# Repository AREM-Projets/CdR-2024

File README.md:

# CdR-2024
Repo contenant l'ensemble des documents liés à la Coupe de France de Robotique (ou CdR pour Coupe de Robotique) 2024.

## Organisation du repo

Le dossier [Generalites](./Generalites) contient l'analyse du règlement ainsi que des ressources diverses. 

Le code, les PCBs et les modélisations 3D sont dans les dossiers PAMIs et Robot, selon leur utilisation.

La documentation associée à chaque partie du projet doit se trouver dans le README du dossier associé.

## Ajout de contenu

N'hésitez pas à ajouter vos tests divers sur ce repo.

Si vous pensez avoir cassé quelque chose, contactez le respo informatique.

## Dates de la CDR : 7 au 11 mai 2024

Merci à tous !!!

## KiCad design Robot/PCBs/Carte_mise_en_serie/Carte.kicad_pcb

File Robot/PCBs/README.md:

# PCBs - Robot principal

Chaque PCB doit être dans un dossier séparé. Il doit être présent à la fois sous la forme d'un schéma modifiable et au formt `.pdf` pour facilité de lecture.

Dans ce README, une description rapide (1-2 lignes) de son utilité doit être présente, ainsi que le nom des personnes qui l'ont designé.

# Liste des PCBs

### PCB n°1: ALIM 5V

Le PCB prend en entrée une tension 24V DC et la convertie en une tension 5V DC. On a 3A par buck et 4 ports de sortie JST-XH, soit 6A max au total pour 8 ports de sortie. La tension de sortie des bucks est réglable grâce au potentiomètre. Ce PCB peut donc être utilisé pour d'autres tension d'entrées et de sorties. De même, on peut récupérer directement le 24V pour les moteurs grâce à un port XT-60.  

Desiger : Cyril, Eliott

### PCB n°2: carte de mise en série

Permet de mettre en série deux batteries 12V.

Designer : Eliott

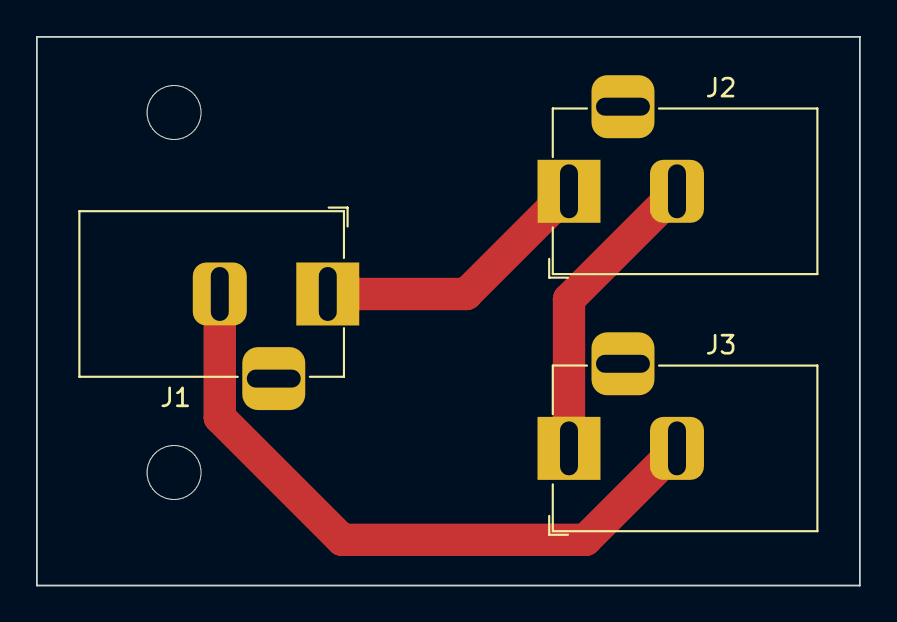
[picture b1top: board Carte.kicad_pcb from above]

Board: 2 copper layers, 45.7 x 30.5 mm, 5 parts (0 on the bottom side), 2 nets.

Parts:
H1, H2: MountingHole; MountingHole_3mm
J1, J2, J3: Conn_01x02_Pin; BarrelJack_Horizontal

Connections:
unnamed: J1.1, J2.1
unnamed: J1.2, J1.3, J2.2, J3.1, J3.2, J3.3

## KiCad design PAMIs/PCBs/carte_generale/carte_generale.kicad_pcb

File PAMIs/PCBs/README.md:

# PCBs - PAMIs

Chaque PCB doit être dans un dossier séparé. Il doit être présent à la fois sous la forme d'un schéma modifiable et au formt `.pdf` pour facilité de lecture.

Dans ce README, une description rapide (1-2 lignes) de son utilité doit être présente, ainsi que le nom des personnes qui l'ont designé.

# Liste des PCBs

### Nom du PCB

Ca sert à quoi ???

Desiger : Quelqu'un, quelqu'un d'autre...

### Nom du PCB n°2

Et lui il sert à quoi ???

Designer : Lui

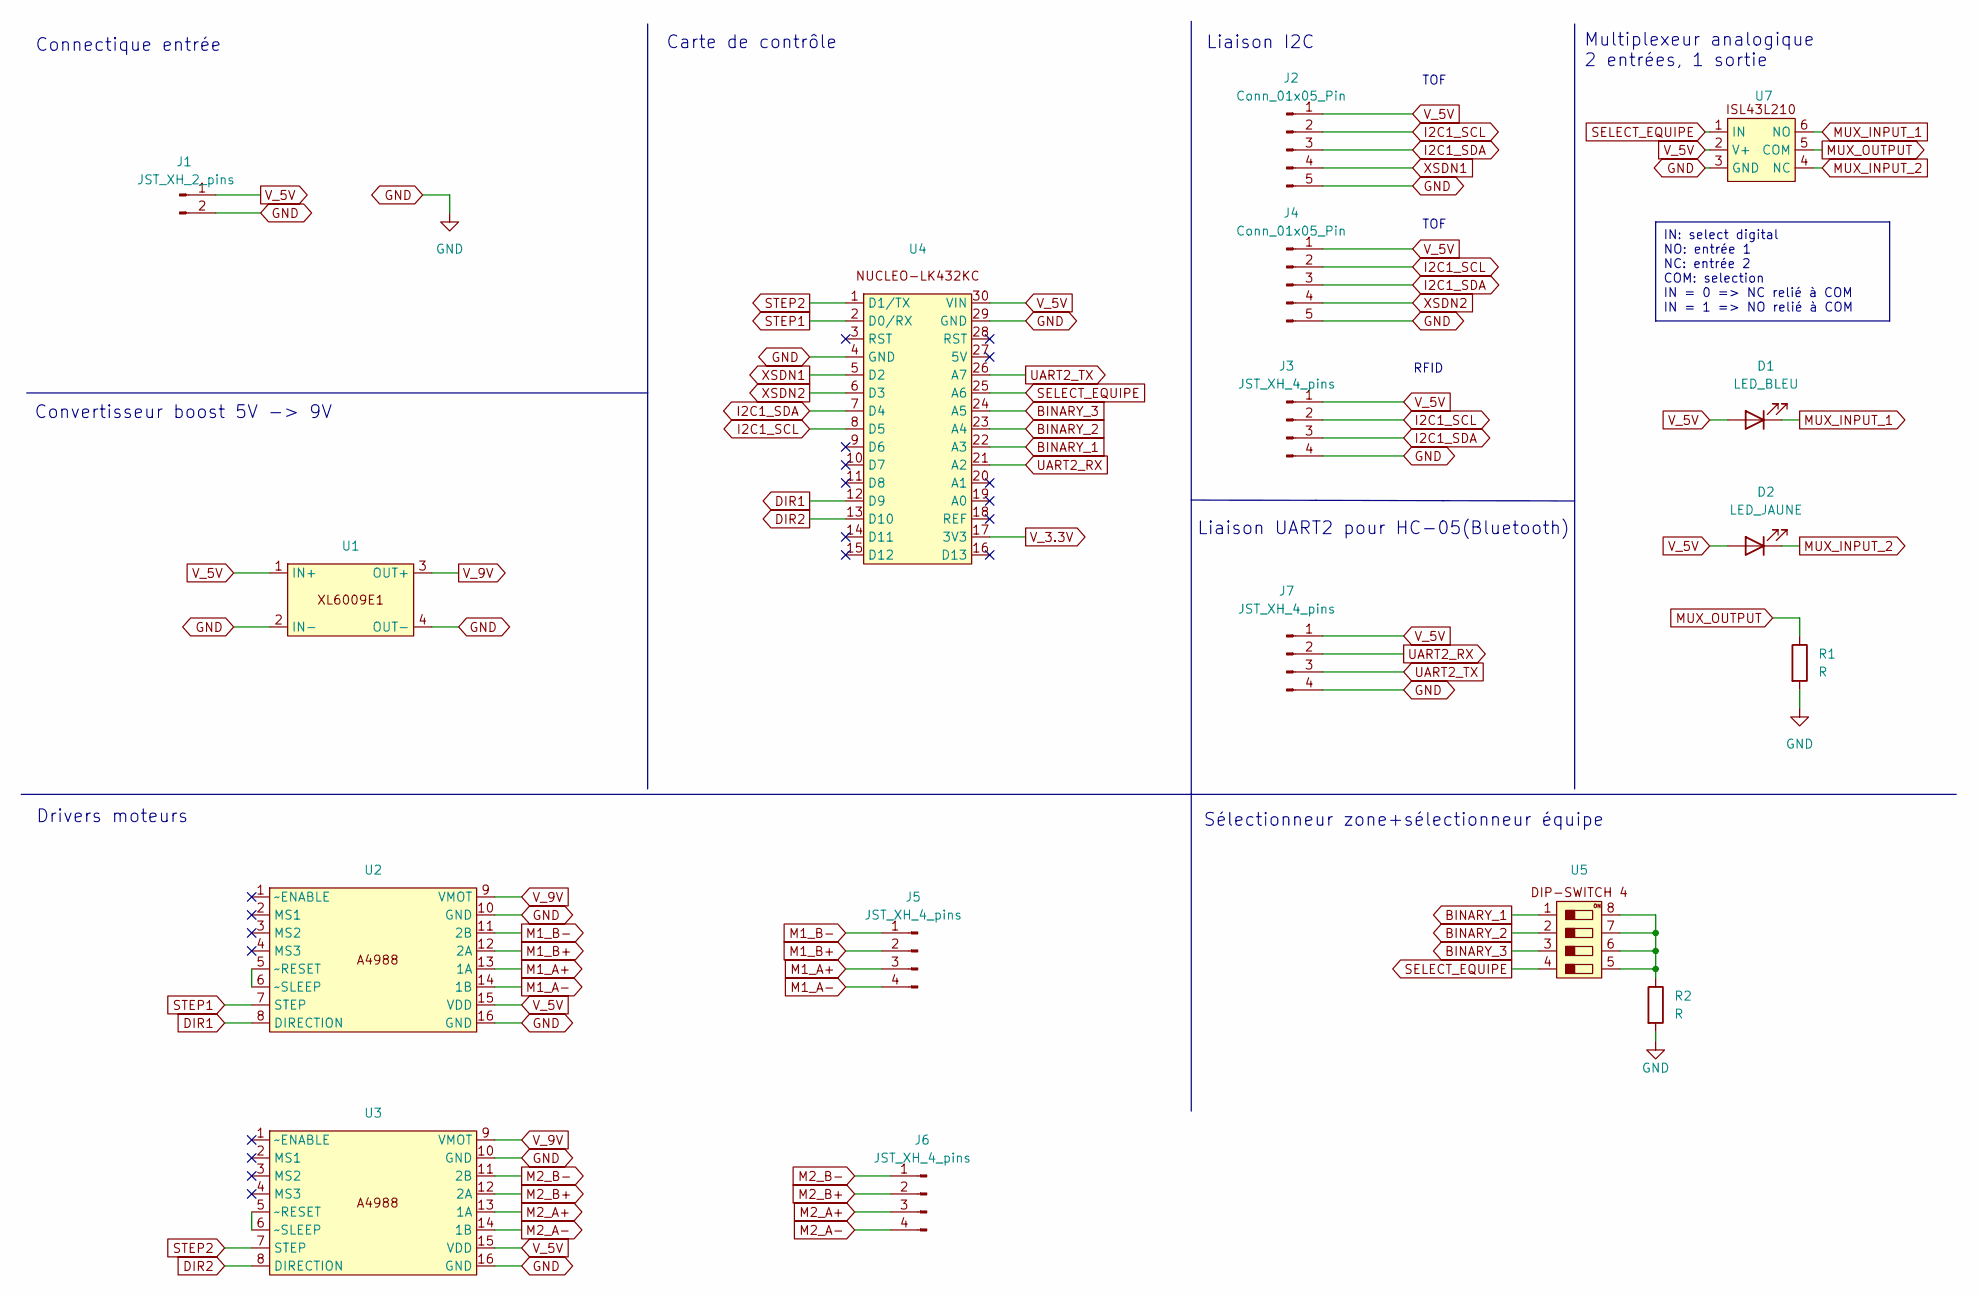
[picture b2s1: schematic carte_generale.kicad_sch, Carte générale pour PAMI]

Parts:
D1: LED_BLEU; LED_D4.0mm
D2: LED_JAUNE; LED_D4.0mm
J1: JST_XH_2_pins; JST_XH_B2B-XH-A_1x02_P2.50mm_Vertical
J2, J4: Conn_01x05_Pin; JST_XH_B5B-XH-A_1x05_P2.50mm_Vertical
J3, J5, J6, J7: JST_XH_4_pins; JST_XH_B4B-XH-A_1x04_P2.50mm_Vertical
R1, R2: R; R_0402_1005Metric
U1: XL6009-E1
U2, U3: MODULE_A4988_STEPPER_MOTOR_DRIVER_CARRIER
U4: MODULE_NUCLEO-L432KC
U5: EDG104S
U7: SOT-363_SC-70-6

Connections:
BINARY_1: U4.22 (A3), U5.1
BINARY_2: U4.23 (A4), U5.2
BINARY_3: U4.24 (A5), U5.3
DIR1: U2.8 (DIRECTION), U4.12 (D9)
DIR2: U3.8 (DIRECTION), U4.13 (D10)
GND: J1.2, J2.5, J3.4, J4.5, J7.4, R1.2, R2.2, U1.2 (IN-), U1.4 (OUT-), U2.10 (GND), U2.16 (GND), U3.10 (GND), U3.16 (GND), U4.4 (GND), U4.29 (GND), U7.3 (GND); also elsewhere on the board
I2C1_SCL: J2.2, J3.2, J4.2, U4.8 (D5)
I2C1_SDA: J2.3, J3.3, J4.3, U4.7 (D4)
M1_A+: J5.3, U2.13 (1A)
M1_A-: J5.4, U2.14 (1B)
M1_B+: J5.2, U2.12 (2A)
M1_B-: J5.1, U2.11 (2B)
M2_A+: J6.3, U3.13 (1A)
M2_A-: J6.4, U3.14 (1B)
M2_B+: J6.2, U3.12 (2A)
M2_B-: J6.1, U3.11 (2B)
MUX_INPUT_1: D1.1 (K), U7.6 (NO)
MUX_INPUT_2: D2.1 (K), U7.4 (NC)
MUX_OUTPUT: R1.1, U7.5 (COM)
unnamed: R2.1, U5.5, U5.6, U5.7, U5.8
unnamed: U2.5 (~RESET), U2.6 (~SLEEP)
unnamed: U3.5 (~RESET), U3.6 (~SLEEP)
SELECT_EQUIPE: U4.25 (A6), U5.4, U7.1 (IN)
STEP1: U2.7 (STEP), U4.2 (D0/RX)
STEP2: U3.7 (STEP), U4.1 (D1/TX)
TIRETTE: U4.20 (A1); also elsewhere on the board
UART2_RX: J7.2, U4.21 (A2)
UART2_TX: J7.3, U4.26 (A7)
V_3.3V: U4.17 (3V3)
V_5V: D1.2 (A), D2.2 (A), J1.1, J2.1, J3.1, J4.1, J7.1, U1.1 (IN+), U2.15 (VDD), U3.15 (VDD), U4.30 (VIN), U7.2 (V+); also elsewhere on the board
V_9V: U1.3 (OUT+), U2.9 (VMOT), U3.9 (VMOT)
XSDN1: J2.4, U4.5 (D2)
XSDN2: J4.4, U4.6 (D3)

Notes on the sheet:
IN: select digital NO: entrée 1 NC: entrée 2 COM: selection IN = 0 => NC relié à COM IN = 1 => NO relié à COM
Drivers moteurs
TOF
Liaison UART2 pour HC-05(Bluetooth)
Convertisseur boost 5V -> 9V
Carte de contrôle
Sélectionneur zone+sélectionneur équipe
RFID
Multiplexeur analogique 2 entrées, 1 sortie
Liaison I2C
Connectique entrée

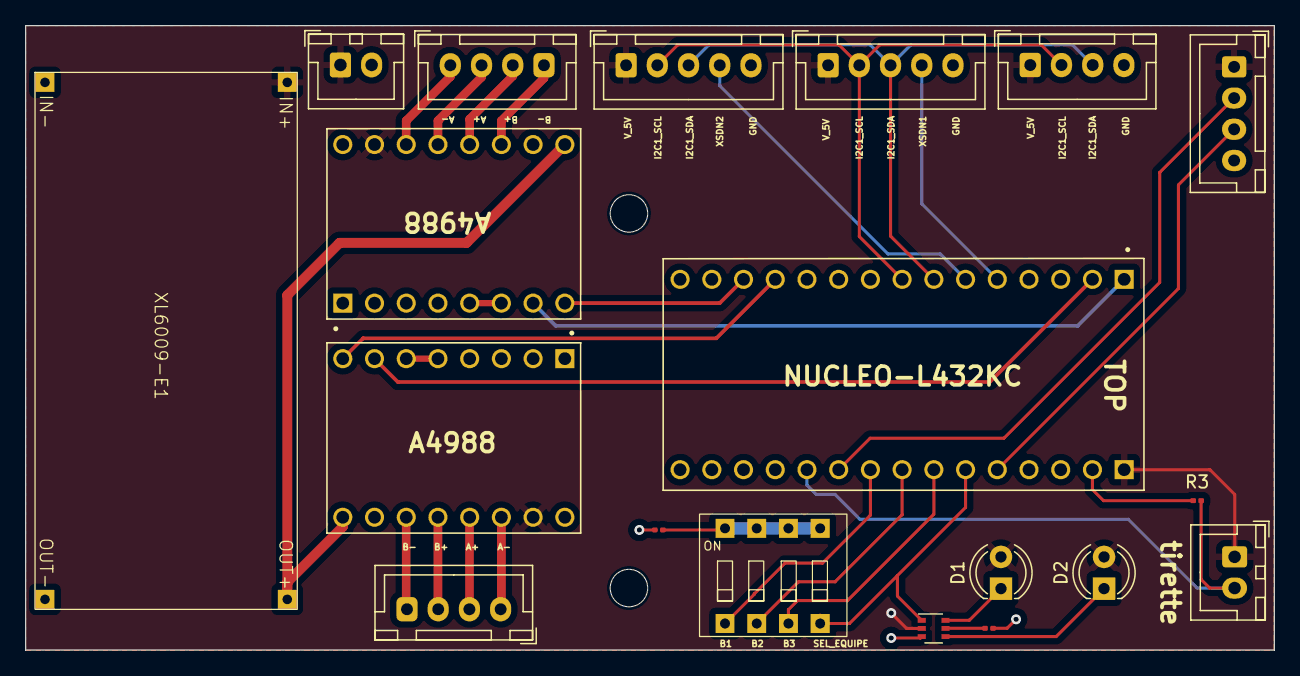
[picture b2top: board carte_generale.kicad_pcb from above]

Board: 2 copper layers, 100.0 x 50.0 mm, 22 parts (0 on the bottom side), 32 nets.

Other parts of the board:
H1, H2: MountingHole; MountingHole_3mm
J8: JST_XH_2_pins; JST_XH_B2B-XH-A_1x02_P2.50mm_Vertical
Logo arem: LOGO; logo_arem
R3: R; R_0201_0603Metric

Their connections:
GND: R3.1; also elsewhere on the board
TIRETTE: J8.2, R3.2; also elsewhere on the board
V_5V: J8.1; also elsewhere on the board

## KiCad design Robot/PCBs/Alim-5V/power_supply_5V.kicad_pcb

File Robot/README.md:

# Robot 

## Actionneur

### Informations utiles pour le pôle actionneur

* Hauteur de la bordure de l'aire de jeu: 70 mm

Plantes:
* Hauteur : 100 mm (env)
* Largeur à la base : 40 mm
* Largeur en haut du pot : 50 mm
* Hauteur du pot : 43 mm 

Pot:
* Largeur à la base: 43 mm
* Largeur en haut: 70 mm
* Hauteur: 65 mm

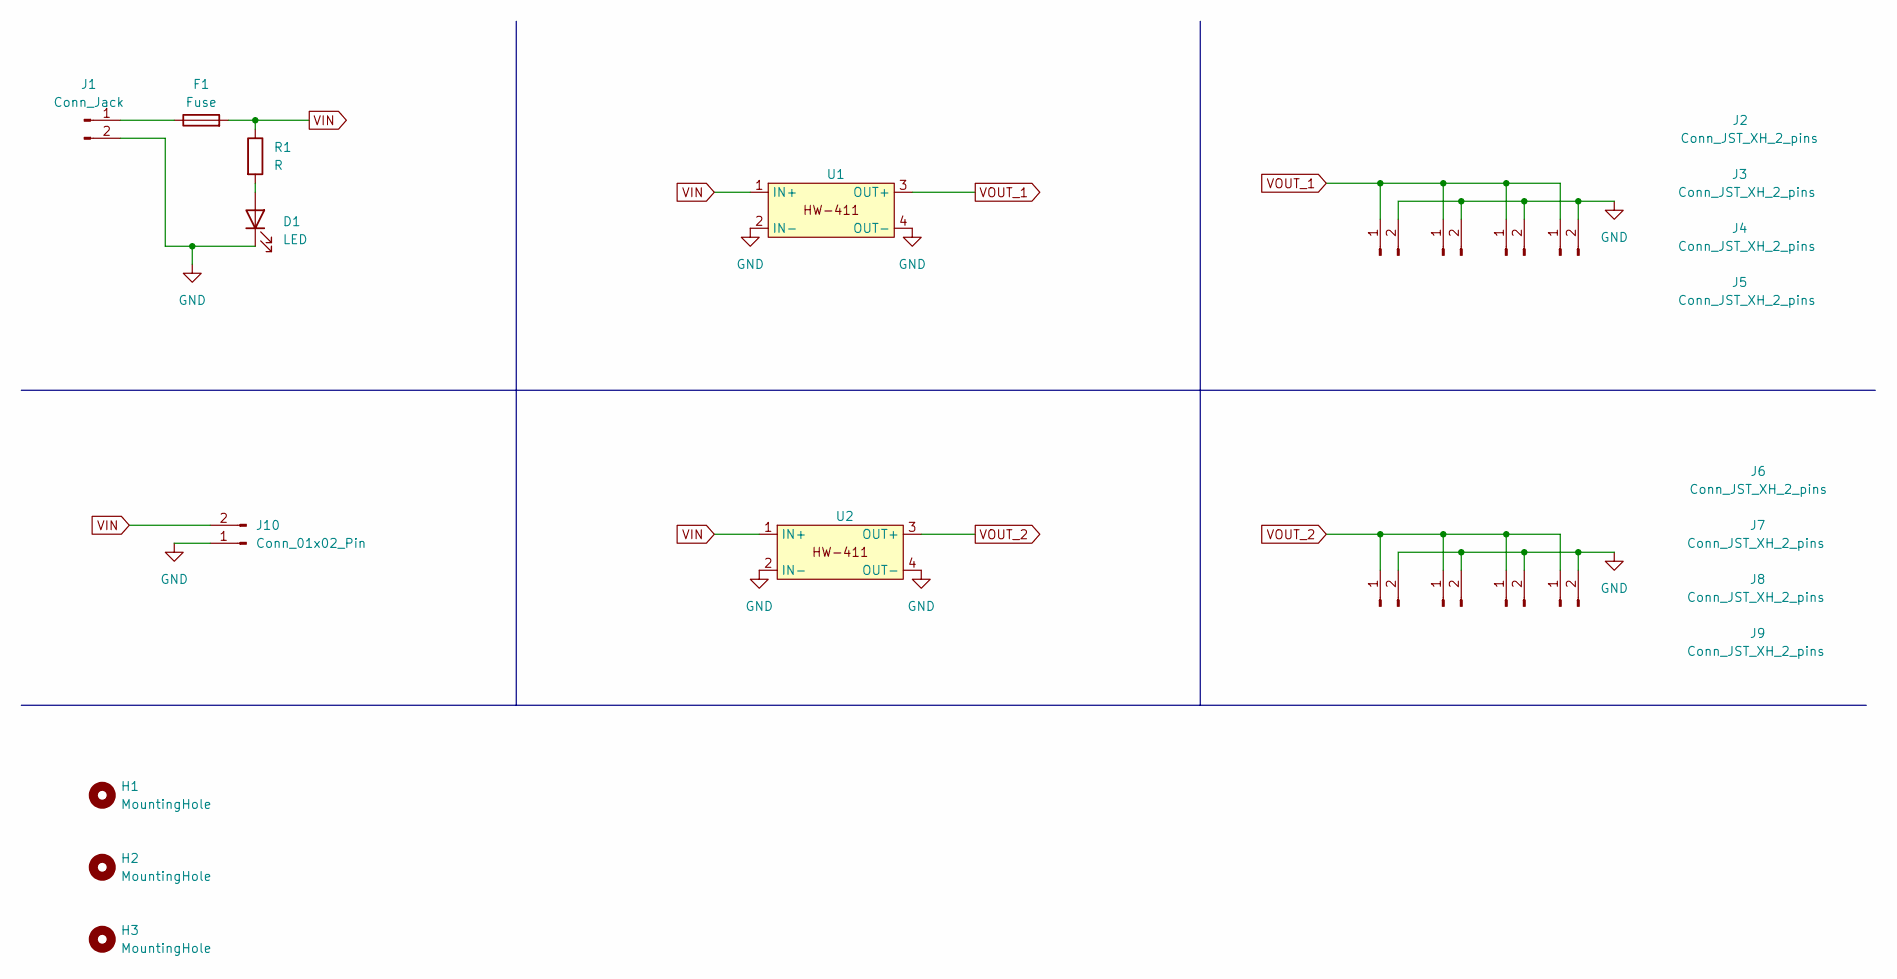
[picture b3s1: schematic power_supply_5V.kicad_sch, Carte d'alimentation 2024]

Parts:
D1: LED; LED_D3.0mm
F1: Fuse; Fuse_BelFuse_0ZRE0100FF_L18.7mm_W5.1mm
H1, H2, H3: MountingHole; MountingHole_3mm
J1: Conn_Jack; BarrelJack_Horizontal
J2, J3, J4, J5, J6, J7, J8, J9: Conn_JST_XH_2_pins; JST_XH_B2B-XH-A_1x02_P2.50mm_Vertical
J10: Conn_01x02_Pin; AMASS_XT60PW-M
R1: R; R_2816_7142Metric
U1, U2: HW_411

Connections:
GND: D1.1 (K), J1.2, J2.2, J3.2, J4.2, J5.2, J6.2, J7.2, J8.2, J9.2, J10.1, U1.2 (IN-), U1.4 (OUT-), U2.2 (IN-), U2.4 (OUT-)
unnamed: D1.2 (A), R1.2
unnamed: F1.1, J1.1
VIN: F1.2, J10.2, R1.1, U1.1 (IN+), U2.1 (IN+)
VOUT_1: J2.1, J3.1, J4.1, J5.1, U1.3 (OUT+)
VOUT_2: J6.1, J7.1, J8.1, J9.1, U2.3 (OUT+)

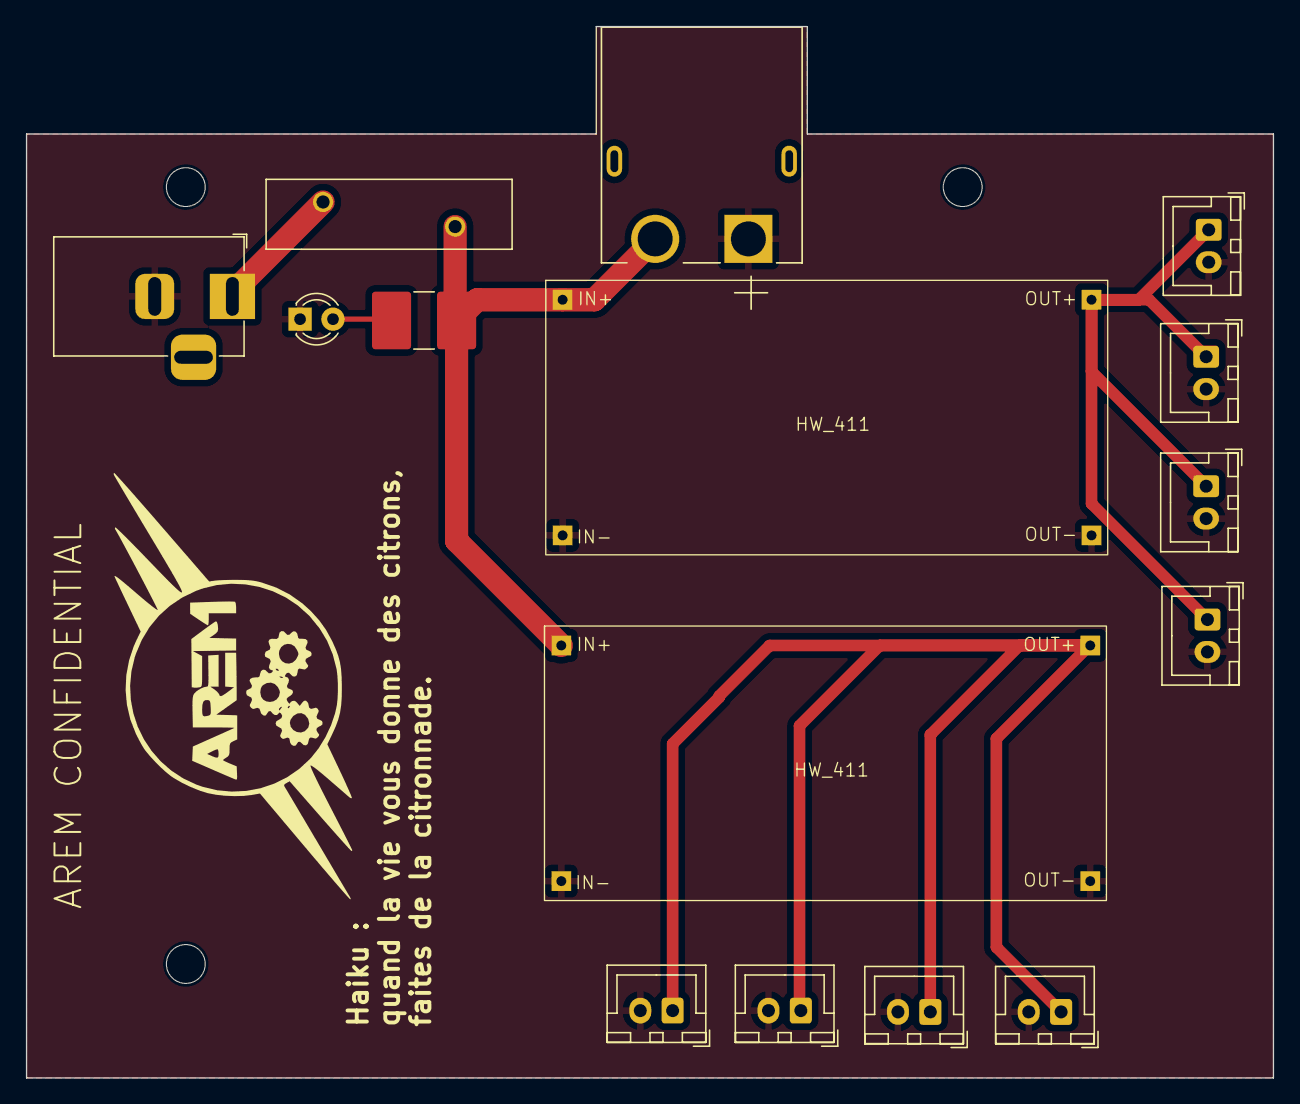
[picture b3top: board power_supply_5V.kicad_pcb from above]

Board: 2 copper layers, 96.3 x 81.2 mm, 19 parts (1 on the bottom side), 6 nets.

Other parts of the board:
He: MountingHole; MountingHole_3mm
Logo arem: LOGO; logo_arem

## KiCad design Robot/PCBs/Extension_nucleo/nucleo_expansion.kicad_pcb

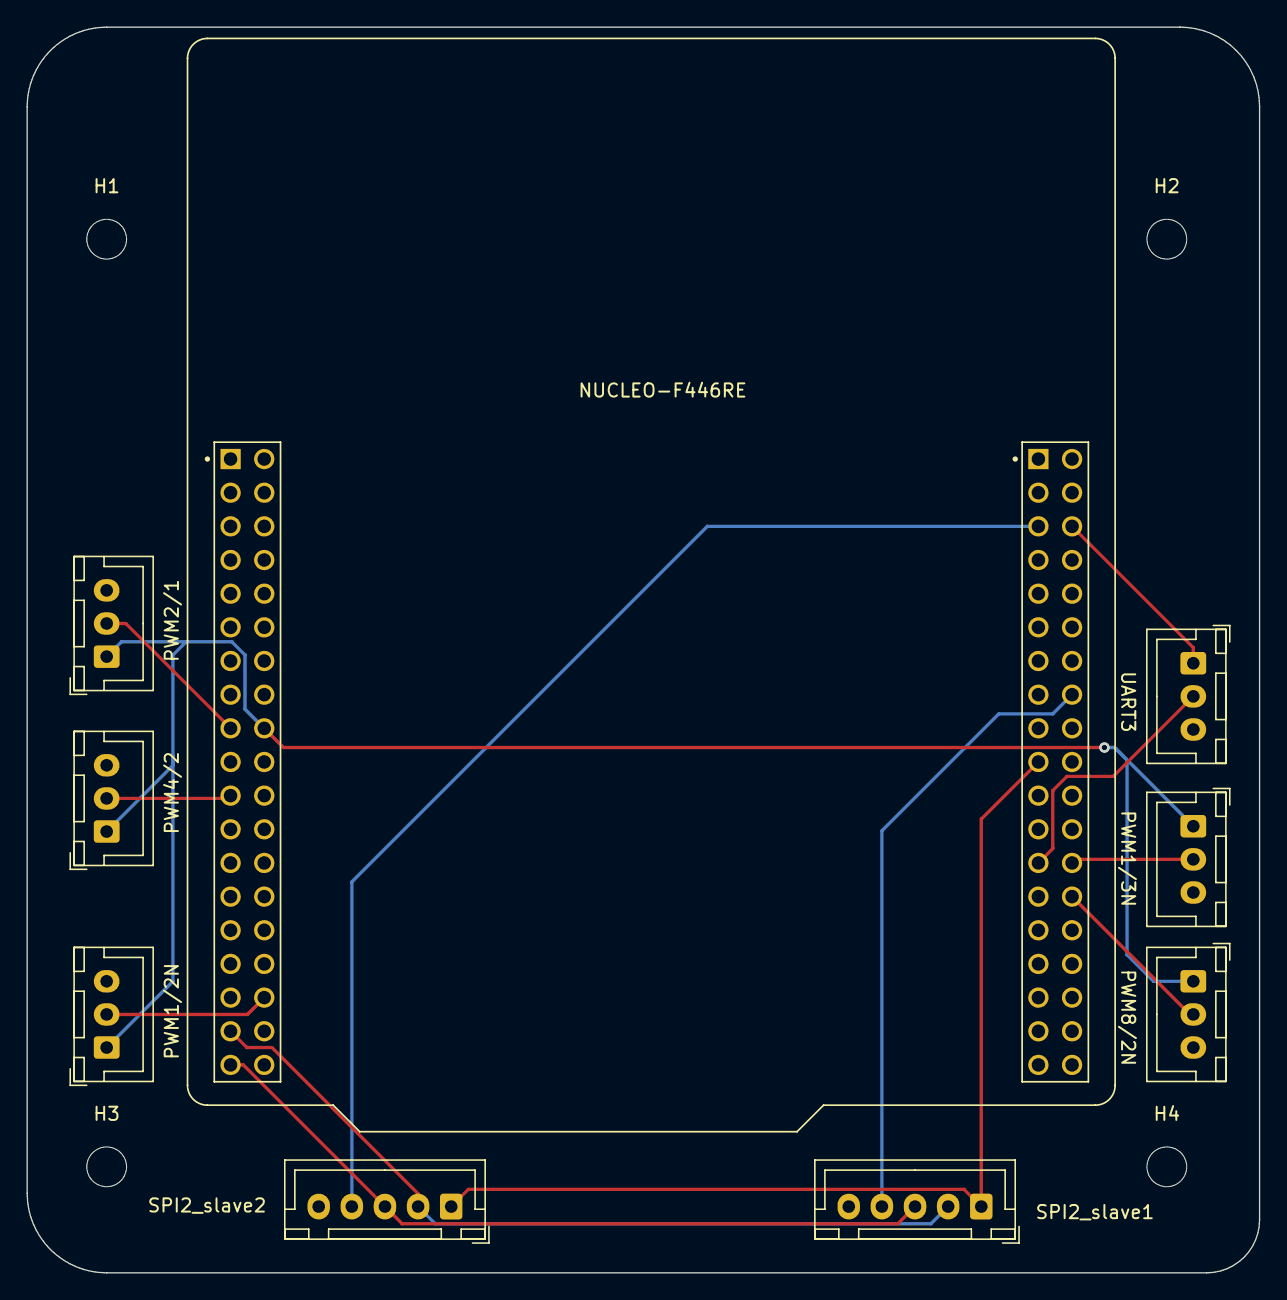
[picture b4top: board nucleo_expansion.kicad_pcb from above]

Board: 2 copper layers, 93.0 x 94.0 mm, 14 parts (0 on the bottom side), 14 nets.

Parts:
H1, H2, H3, H4: MountingHole; MountingHole_3mm
J1: SPI2_slave1; JST_XH_B5B-XH-A_1x05_P2.50mm_Vertical
J2: SPI2_slave2; JST_XH_B5B-XH-A_1x05_P2.50mm_Vertical
J3: UART3; JST_XH_B3B-XH-A_1x03_P2.50mm_Vertical
J4: PWM2/1; JST_XH_B3B-XH-A_1x03_P2.50mm_Vertical
J5: PWM4/2; JST_XH_B3B-XH-A_1x03_P2.50mm_Vertical
J6: PWM1/2N; JST_XH_B3B-XH-A_1x03_P2.50mm_Vertical
J7: PWM1/3N; JST_XH_B3B-XH-A_1x03_P2.50mm_Vertical
J8: PWM8/2N; JST_XH_B3B-XH-A_1x03_P2.50mm_Vertical
Logo arem: LOGO; logo_arem
U1: NUCLEO-F446RE; MODULE_NUCLEO-F446RE

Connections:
+5V: J4.1, J5.1, J6.1, J7.1, J8.1, U1.CN7_18 (CN7_+5V)
GND: J1.5, J2.5, J3.3, J4.3, J5.3, J6.3, J7.3, J8.3, U1.CN7_8 (CN7_GND), U1.CN7_19 (CN7_GND), U1.CN7_20 (CN7_GND), U1.CN7_22 (CN7_GND), U1.CN10_9 (CN10_GND), U1.CN10_20 (CN10_GND), U1.CN10_32 (AGND)
PWM1/2N: J6.2, U1.CN7_34 (PB0)
PWM1/3N: J7.2, U1.CN10_26 (PB15)
PWM2/1: J4.2, U1.CN7_17 (PA15)
PWM4/2: J5.2, U1.CN7_21 (PB7)
PWM8/2N: J8.2, U1.CN10_28 (PB14)
SPI2_CS1: J1.4, U1.CN10_16 (PB12)
SPI2_CS2: J2.4, U1.CN10_5 (PB9)
SPI2_MISO: J1.2, J2.2, U1.CN7_35 (PC2)
SPI2_MOSI: J1.3, J2.3, U1.CN7_37 (PC3)
SPI2_SCK: J1.1, J2.1, U1.CN10_19 (PC7)
UART3_RX: J3.1, U1.CN10_6 (PC5)
UART3_TX: J3.2, U1.CN10_25 (PB10)

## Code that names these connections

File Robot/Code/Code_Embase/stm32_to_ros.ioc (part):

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Mcu.Name=STM32F446R(C-E)Tx
Mcu.Package=LQFP64
Mcu.UserName=STM32F446RETx
PA10.GPIOParameters=GPIO_Label
PA10.GPIO_Label=ssel2
PA10.Signal=GPIO_Output
PA13.GPIOParameters=GPIO_Label
PA13.GPIO_Label=TMS
PA13.Mode=Serial_Wire
PA13.Signal=SYS_JTMS-SWDIO
PA14.GPIOParameters=GPIO_Label
PA14.GPIO_Label=TCK
PA14.Mode=Serial_Wire
PA14.Signal=SYS_JTCK-SWCLK
PA15.Signal=S_TIM2_CH1_ETR
PA2.GPIOParameters=GPIO_Label
PA2.GPIO_Label=USART_TX
PA2.Mode=Asynchronous
PA2.Signal=USART2_TX
PA3.GPIOParameters=GPIO_Label
PA3.GPIO_Label=USART_RX
PA3.Mode=Asynchronous
PA3.Signal=USART2_RX
PA4.GPIOParameters=GPIO_Label
PA4.GPIO_Label=ssel1
PA4.Signal=GPIO_Output
PA5.GPIOParameters=GPIO_Label
PA5.GPIO_Label=LD2 [Green Led]
PA5.Signal=GPIO_Output
PA6.Mode=Full_Duplex_Master
PA6.Signal=SPI1_MISO
PA7.Mode=Full_Duplex_Master
PA7.Signal=SPI1_MOSI
PB0.Mode=PWM Generation2 CH2N
PB0.Signal=TIM1_CH2N
PB10.Mode=Asynchronous
PB10.Signal=USART3_TX
PB12.Signal=GPIO_Output
PB14.Mode=PWM Generation2 CH2N
PB14.Signal=TIM8_CH2N
PB15.Mode=PWM Generation3 CH3N
PB15.Signal=TIM1_CH3N
PB3.Mode=Full_Duplex_Master
PB3.Signal=SPI1_SCK
PB4.GPIOParameters=GPIO_Label
PB4.GPIO_Label=reset_shield_2
PB4.Signal=GPIO_Output
PB5.GPIOParameters=GPIO_Label
PB5.GPIO_Label=reset_shield_1
PB5.Signal=GPIO_Output
PB7.Signal=S_TIM4_CH2
PB9.Signal=GPIO_Output
PC13.GPIOParameters=GPIO_Label,GPIO_ModeDefaultEXTI
PC13.GPIO_Label=B1 [Blue PushButton]
PC13.GPIO_ModeDefaultEXTI=GPIO_MODE_IT_FALLING
PC13.Signal=GPXTI13
PC14-OSC32_IN.Mode=LSE-External-Oscillator
PC14-OSC32_IN.Signal=RCC_OSC32_IN
PC15-OSC32_OUT.Mode=LSE-External-Oscillator
PC15-OSC32_OUT.Signal=RCC_OSC32_OUT
PC2.Mode=Full_Duplex_Master
PC2.Signal=SPI2_MISO
PC3.Mode=Full_Duplex_Master
PC3.Signal=SPI2_MOSI
PC5.Mode=Asynchronous
PC5.Signal=USART3_RX
PC7.Mode=Full_Duplex_Master
PC7.Signal=SPI2_SCK
PH0-OSC_IN.Mode=HSE-External-Oscillator
PH0-OSC_IN.Signal=RCC_OSC_IN
PH1-OSC_OUT.Mode=HSE-External-Oscillator
PH1-OSC_OUT.Signal=RCC_OSC_OUT
RCC.HSE_VALUE=8000000
RCC.SYSCLKFreq_VALUE=180000000
RCC.SYSCLKSource=RCC_SYSCLKSOURCE_PLLCLK
board=NUCLEO-F446RE
boardIOC=true

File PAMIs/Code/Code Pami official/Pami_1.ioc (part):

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Mcu.Name=STM32L432K(B-C)Ux
Mcu.Package=UFQFPN32
Mcu.UserName=STM32L432KCUx
PA0.GPIOParameters=GPIO_Label
PA0.GPIO_Label=MCO [High speed clock in]
PA0.Mode=HSE-External-Clock-Source-for-LittleOrca
PA0.Signal=RCC_CK_IN
PA10.GPIOParameters=GPIO_Label
PA10.GPIO_Label=PWM1
PA10.Signal=S_TIM1_CH3
PA11.GPIOParameters=GPIO_Label
PA11.GPIO_Label=DIR2
PA11.Signal=GPIO_Output
PA13\ (JTMS-SWDIO).GPIOParameters=GPIO_Label
PA13\ (JTMS-SWDIO).GPIO_Label=SWDIO
PA13\ (JTMS-SWDIO).Mode=Serial_Wire
PA13\ (JTMS-SWDIO).Signal=SYS_JTMS-SWDIO
PA14\ (JTCK-SWCLK).GPIOParameters=GPIO_Label
PA14\ (JTCK-SWCLK).GPIO_Label=SWCLK
PA14\ (JTCK-SWCLK).Mode=Serial_Wire
PA14\ (JTCK-SWCLK).Signal=SYS_JTCK-SWCLK
PA15\ (JTDI).GPIOParameters=GPIO_Label
PA15\ (JTDI).GPIO_Label=VCP_RX
PA15\ (JTDI).Mode=Asynchronous
PA15\ (JTDI).Signal=USART2_RX
PA2.GPIOParameters=GPIO_Label
PA2.GPIO_Label=VCP_TX
PA2.Mode=Asynchronous
PA2.Signal=USART2_TX
PA8.GPIOParameters=GPIO_Label
PA8.GPIO_Label=DIR1
PA8.Signal=GPIO_Output
PA9.GPIOParameters=GPIO_Label
PA9.GPIO_Label=PWM2
PA9.Signal=S_TIM1_CH2
PB0.GPIOParameters=GPIO_Label
PB0.GPIO_Label=ECHO
PB0.Signal=GPXTI0
PB1.GPIOParameters=GPIO_Label
PB1.GPIO_Label=TRIG
PB1.Signal=GPIO_Output
PB3\ (JTDO-TRACESWO).GPIOParameters=GPIO_Label
PB3\ (JTDO-TRACESWO).GPIO_Label=LD3 [Green]
PB3\ (JTDO-TRACESWO).Signal=GPIO_Output
PB5.GPIOParameters=GPIO_PuPd,GPIO_Label
PB5.GPIO_Label=TIRETTE
PB5.GPIO_PuPd=GPIO_PULLDOWN
PB5.Signal=GPXTI5
PC14-OSC32_IN\ (PC14).Mode=LSE-External-Oscillator
PC14-OSC32_IN\ (PC14).Signal=RCC_OSC32_IN
PC15-OSC32_OUT\ (PC15).Mode=LSE-External-Oscillator
PC15-OSC32_OUT\ (PC15).Signal=RCC_OSC32_OUT
RCC.HSE_VALUE=8000000
RCC.SYSCLKFreq_VALUE=72000000
RCC.SYSCLKSource=RCC_SYSCLKSOURCE_PLLCLK
board=NUCLEO-L432KC
boardIOC=true

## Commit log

2023-11-17 Ajout dossiers
2023-11-17 j'ai mis des README partout
2023-11-20 update des README
2023-11-25 ajout cdcf
2023-11-25 ajout schéma contraintes
2023-11-25 ajout points
2023-11-30 Ajout conception PAMIs + rangement
2023-12-02 refactor
2023-12-02 ajout liens utiles
2023-12-02 rangement liens
2023-12-02 rename
2023-12-02 Ajout embase 2023
2023-12-02 embase 3 roues
2024-01-20 ajout schema elec PAMI
2024-01-20 taille composants
2024-01-20 README Pamis
2024-01-23 When in doubt, RTFM
2024-01-24 code pami test
2024-01-27 Ajout limite 10s
2024-02-03 update reglement
2024-02-08 carte alim v1 partial deposit
2024-02-10 Ajout roues PAMI
2024-02-10 Carte mise en serie
2024-02-10 ajout alim 5V
2024-02-10 mise a jour carte serie
2024-02-10 Create Support-batterie 3D
2024-02-12 Upload Support-batterie
2024-02-21 added debug info
2024-02-22 ajout code embase
2024-02-22 Rectification support batterie
2024-02-22 readme alim
2024-03-15 Code raspi4 et stm32 capteurs et actionneurs
2024-03-15 Premiere proposition de code pour le capteur RFID des pamis
2024-03-18 PCB PAMI + carte d'extension Nucleo-64
2024-03-20 1ere définiton API embase
2024-03-29 ajout gerber pour les pcb carte d'extention nucléo et pami
2024-03-29 logo_pcb_robot_grb
2024-03-29 29_04_24
2024-03-29 Commit 1 du pcb pamis commandé
2024-03-29 correction DRC
2024-04-02 Ajout partie actionneurs + infos dans readme robot
2024-04-03 Nouvel espace - conclusion CDR
2024-04-03 New respository for CDR day
2024-04-03 Base du code PAMI
2024-04-15 Changement de nom et 3D PAMI
2024-04-22 Code actionneur avec 1 TOF Fiable
2024-04-22 Retrait de fichiers pas concernes par cette branche et a l'origine de conflits (PCB)
2024-04-22 ajout des fichiers supprimes a l'origine de conflits
2024-04-23 Nouveaux composants du PAMI
2024-04-26 ajout gestion deuxieme tof
2024-04-28 Update code embase + command parser
2024-04-28 Changement de nom
2024-04-29 Fin du modèle 3D du PAMI
2024-04-30 Mise a jour code raspi (tirette, selecteur equipe, affichage score)
2024-04-30 mise a jour code raspi4: tirette, selecteur equipe, affichage score
2024-05-02 Mise a jour code embase avec tirette et selecteur equipe
2024-05-03 corrections pour la tirette et ajout commentaires
2024-05-04 Temporisations OK
2024-05-06 rotation cassée, UART ok
2024-05-06 modif pin selecteur equipe + piece tirette + pinout raspi4 pio
2024-05-07 UART + movement OK
2024-05-07 fini ?
2024-05-07 correction
2024-05-07 correction + comments
2024-05-08 maj code pami et code embase
2024-05-08 maj pami et Embase
2024-05-08 code embase et pamis
2024-05-08 Réparation de git
2024-05-08 Code V1 PAMI sur base mathieu
2024-05-08 mise a jour code actionneur sans le tof1
2024-05-08 code homologation
2024-05-08 mise au point communication embase raspi pour les matchs. version avec que equipe bleue !
2024-05-08 fix FOV
2024-05-08 amelioration affichage equipe 1
2024-05-09 correction ordre initialisation embase
2024-05-09 test global equipe
2024-05-09 test file_equipe_v1
2024-05-09 retrait fov
2024-05-09 score 25
2024-05-09 FOV avant et arriere en fonction equipe
2024-05-09 fix sens fov jaune bleu
2024-05-09 fix fov 2
2024-05-09 fix arret 90s 1
2024-05-09 fix : retrait wait avant init
2024-05-09 double init
2024-05-09 correctif pts match 2
2024-05-09 retrait double init
2024-05-09 ajout redemarrage apres arret par detecction lidar (v1)
2024-05-10 code fiable sans redemarrage apres arret par detection lidar
2024-05-10 modif detection lidar
2024-05-10 nouvelle version evitement lidar (FOV 100, Dist 35cm)
2024-05-10 25 pts
2024-05-10 modif detection lidar et redemarrage v1
2024-05-10 ajout timing apres arret embase sur danger trop eleve
2024-05-10 switch to strat 6 panneaux
2024-05-10 fix elea
2024-05-10 fix temps entre mesures
2024-05-10 fix utilisation angles mesures plutot que dates
2024-05-10 3 panneaux
2024-05-10 version match 4 fiable avec lidar et reprise de mouvement
2024-05-11 todo cdr2025
2024-09-30 version fete de la science 2024 (foreuse vers le bas)
2024-09-30 retrait de matiere sur piece (version FDS 2024)
2024-10-03 update FDS foreuse
